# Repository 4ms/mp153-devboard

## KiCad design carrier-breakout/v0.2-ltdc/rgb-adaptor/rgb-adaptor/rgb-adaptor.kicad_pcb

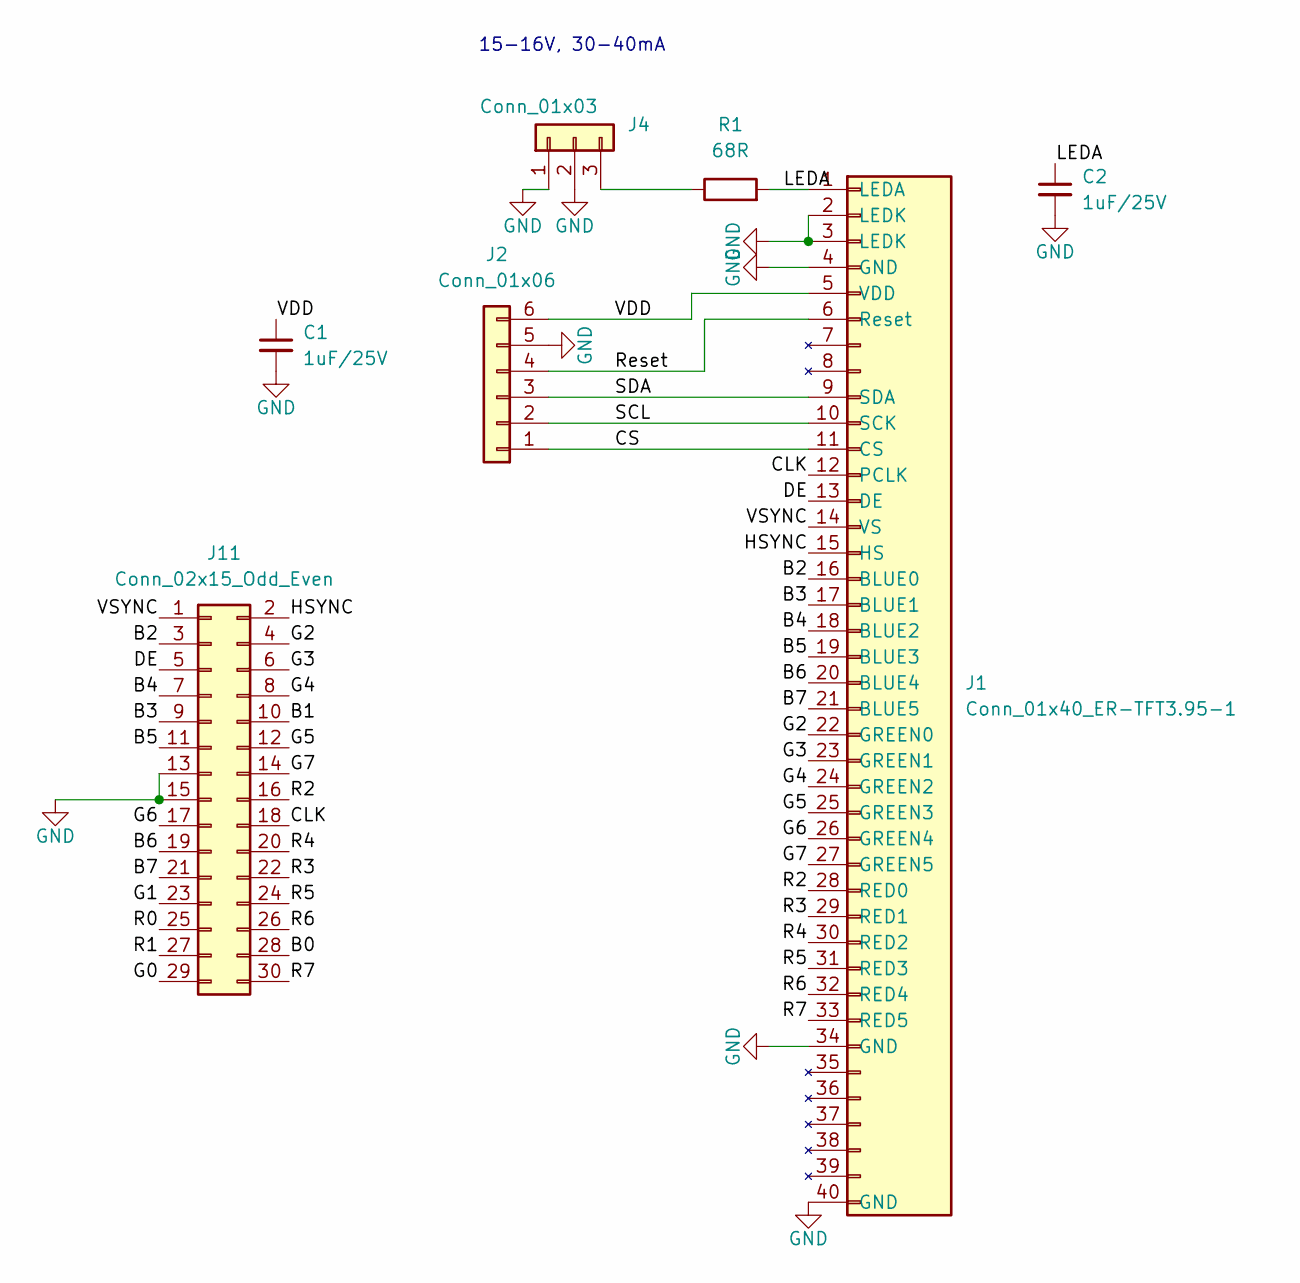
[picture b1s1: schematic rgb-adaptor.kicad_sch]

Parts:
C1, C2: 1uF_0603_25V; C_0603; Part Number GRM188R61E105KA12D; JLCPCB ID C15849
J1: Conn_01x40_ER-TFT3.95-1; Amphenol_F32R-1A7x1-11040_1x40-1MP_P0.5mm_Horizontal; Part Number ER-TFT3.95-1
J2: Conn_01x06; Pins_1x06_2.54mm_TH_SWD; Part Number 1-0601FBV0T
J4: Conn_01x03; Pins_1x03_2.54mm_TH; Part Number 1-0301FBV0T
J11: Conn_02x15_Odd_Even; PinSocket_2x15_P2.54mm_Vertical
R1: 68R_0603; R_0603; Part Number RC0603FR-0768RL; JLCPCB ID C27592

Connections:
/B0: J11.28
/B1: J11.10
/B2: J1.16 (BLUE0), J11.3
/B3: J1.17 (BLUE1), J11.9
/B4: J1.18 (BLUE2), J11.7
/B5: J1.19 (BLUE3), J11.11
/B6: J1.20 (BLUE4), J11.19
/B7: J1.21 (BLUE5), J11.21
/CLK: J1.12 (PCLK), J11.18
/CS: J1.11 (CS), J2.1
/DE: J1.13 (DE), J11.5
/G0: J11.29
/G1: J11.23
/G2: J1.22 (GREEN0), J11.4
/G3: J1.23 (GREEN1), J11.6
/G4: J1.24 (GREEN2), J11.8
/G5: J1.25 (GREEN3), J11.12
/G6: J1.26 (GREEN4), J11.17
/G7: J1.27 (GREEN5), J11.14
/HSYNC: J1.15 (HS), J11.2
/LEDA: C2.1, J1.1 (LEDA), R1.2
/R0: J11.25
/R1: J11.27
/R2: J1.28 (RED0), J11.16
/R3: J1.29 (RED1), J11.22
/R4: J1.30 (RED2), J11.20
/R5: J1.31 (RED3), J11.24
/R6: J1.32 (RED4), J11.26
/R7: J1.33 (RED5), J11.30
/Reset: J1.6 (Reset), J2.4
/SCL: J1.10 (SCK), J2.2
/SDA: J1.9 (SDA), J2.3
/VDD: C1.1, J1.5 (VDD), J2.6
/VSYNC: J1.14 (VS), J11.1
GND: C1.2, C2.2, J1.2 (LEDK), J1.3 (LEDK), J1.4 (GND), J1.34 (GND), J1.40 (GND), J2.5, J4.1, J4.2, J11.13, J11.15
unnamed: J4.3, R1.1

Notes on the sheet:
15-16V, 30-40mA

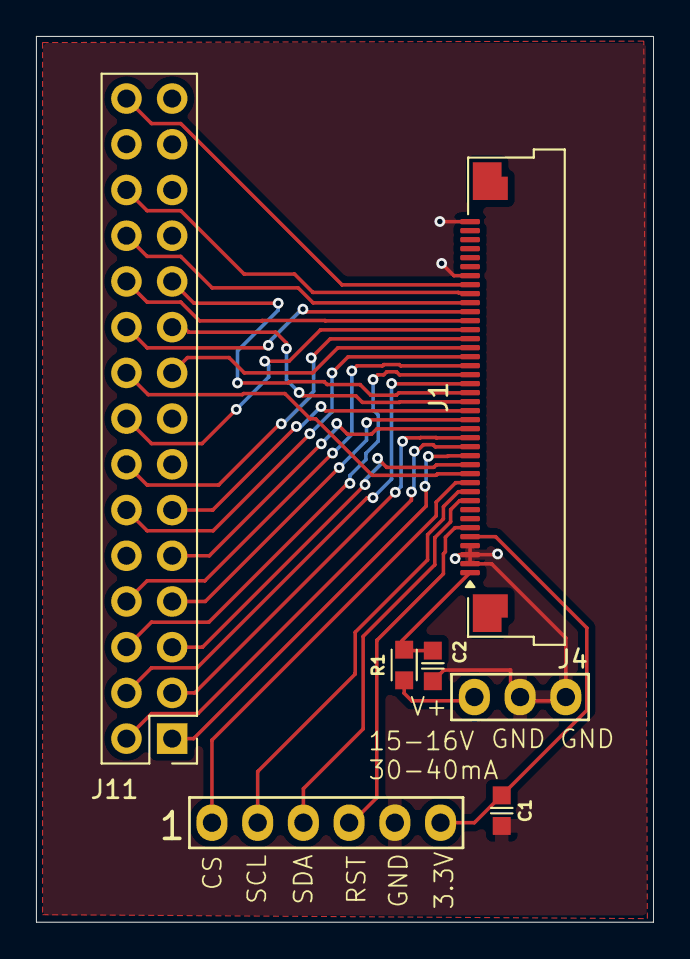
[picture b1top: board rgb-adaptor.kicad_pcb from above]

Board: 2 copper layers, 34.3 x 49.2 mm, 7 parts (0 on the bottom side), 30 nets.
